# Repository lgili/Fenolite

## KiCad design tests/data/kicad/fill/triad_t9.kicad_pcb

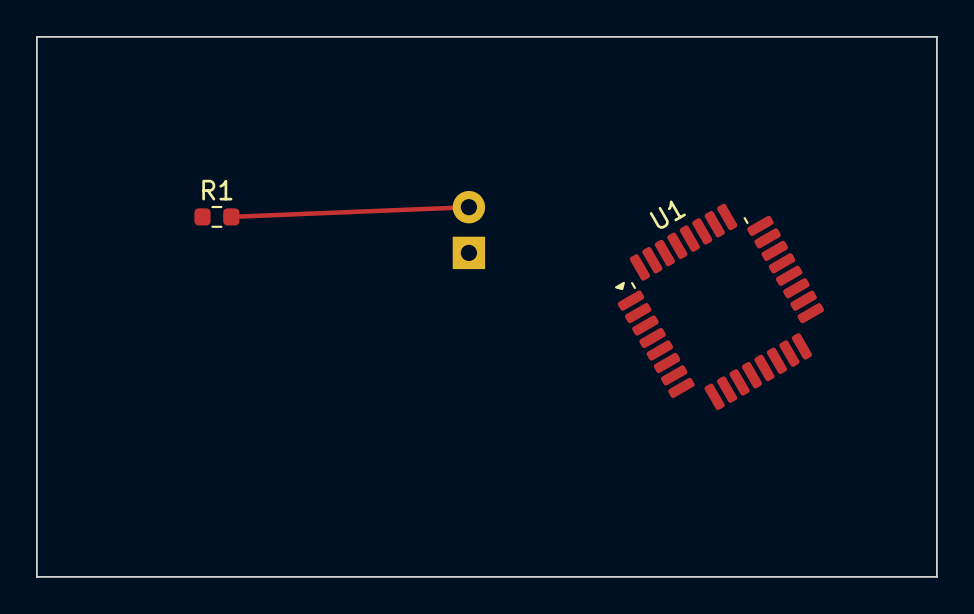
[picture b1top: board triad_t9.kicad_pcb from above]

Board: 2 copper layers, 50.0 x 30.0 mm, 3 parts (1 on the bottom side), 3 nets.

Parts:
D1: LED; Mini_LED_THT_3mm
R1: 1k; Mini_R_0603
U1: MCU; Mini_QFP-32_7x7mm_P0.8mm

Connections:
GND: D1.1, U1.9
LED_A: D1.2, R1.2
VIN: R1.1, U1.1
